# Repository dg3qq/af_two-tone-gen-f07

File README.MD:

# AF-TWO-TONE-GENERATOR

##### cc-by-sa-nc DG3QQ rodi
##### rev. mar. 2024

# Bastel-Projekt zum 14. Giessener Amateurfunk Tag

+ [expose](F07-project/_expose.md]
+ video interview by Kirk (DO3KI) [14. Gießener Amateurfunktreffen 2024 - Doppeltongenerator Bauprojekt & ARRL Prüfung USA Rufzeichen](https://www.youtube.com/watch?v=AF0V_h3_ksM)

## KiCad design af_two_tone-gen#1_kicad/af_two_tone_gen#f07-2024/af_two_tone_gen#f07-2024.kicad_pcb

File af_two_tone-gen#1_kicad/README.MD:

# Two-Tone-Generator by DG3QQ 

#### copyright: dg3qq (cc-by-sa)

## PCB in KiCad 

This was an attempt to port PCB development to KiCad. However, due to time constraints it was abandoned.

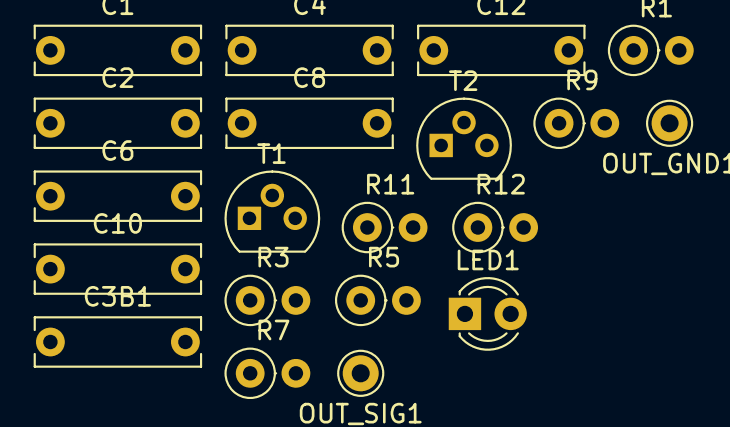
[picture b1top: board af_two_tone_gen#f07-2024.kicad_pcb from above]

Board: 2 copper layers, 20 parts (0 on the bottom side), 8 nets, no tracks yet.

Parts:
C1: C-EU025_050-025X075; C_Rect_L9.0mm_W2.5mm_P7.50mm_MKT
C2, C6: 22n; C_Rect_L9.0mm_W2.5mm_P7.50mm_MKT
C3B1, C12: 3n3; C_Rect_L9.0mm_W2.5mm_P7.50mm_MKT
C4, C8: 10n; C_Rect_L9.0mm_W2.5mm_P7.50mm_MKT
C10: 4n7; C_Rect_L9.0mm_W2.5mm_P7.50mm_MKT
LED1: LED3MM; LED_D3.0mm
OUT_GND1: PINHD-1X1; Pin_D1.0mm_L10.0mm
OUT_SIG1: PINHD-1X1; Pin_D1.0mm_L10.0mm
R1: R-EU_0207_2V; R_Axial_DIN0207_L6.3mm_D2.5mm_P2.54mm_Vertical
R3: 47k; R_Axial_DIN0207_L6.3mm_D2.5mm_P2.54mm_Vertical
R5, R11: 2k2; R_Axial_DIN0207_L6.3mm_D2.5mm_P2.54mm_Vertical
R7: 4k7; R_Axial_DIN0207_L6.3mm_D2.5mm_P2.54mm_Vertical
R9: 33k; R_Axial_DIN0207_L6.3mm_D2.5mm_P2.54mm_Vertical
R12: 10k; R_Axial_DIN0207_L6.3mm_D2.5mm_P2.54mm_Vertical
T1, T2: 2n3904; TO-92

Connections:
+3V3: C1.2, R1.2, R5.2, R11.2
GND: C1.1, C2.1, C6.2, C8.1, C12.2, OUT_GND1.1
unnamed: C2.2, R3.2
unnamed: C3B1.1, R3.1, R5.1
unnamed: C6.1, R7.1
unnamed: C8.2, R9.2
unnamed: R9.1, R11.1
unnamed: C12.1, R12.2

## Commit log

2024-04-06 initial
